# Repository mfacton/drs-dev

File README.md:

# drs-dev
Active Aero Development Board

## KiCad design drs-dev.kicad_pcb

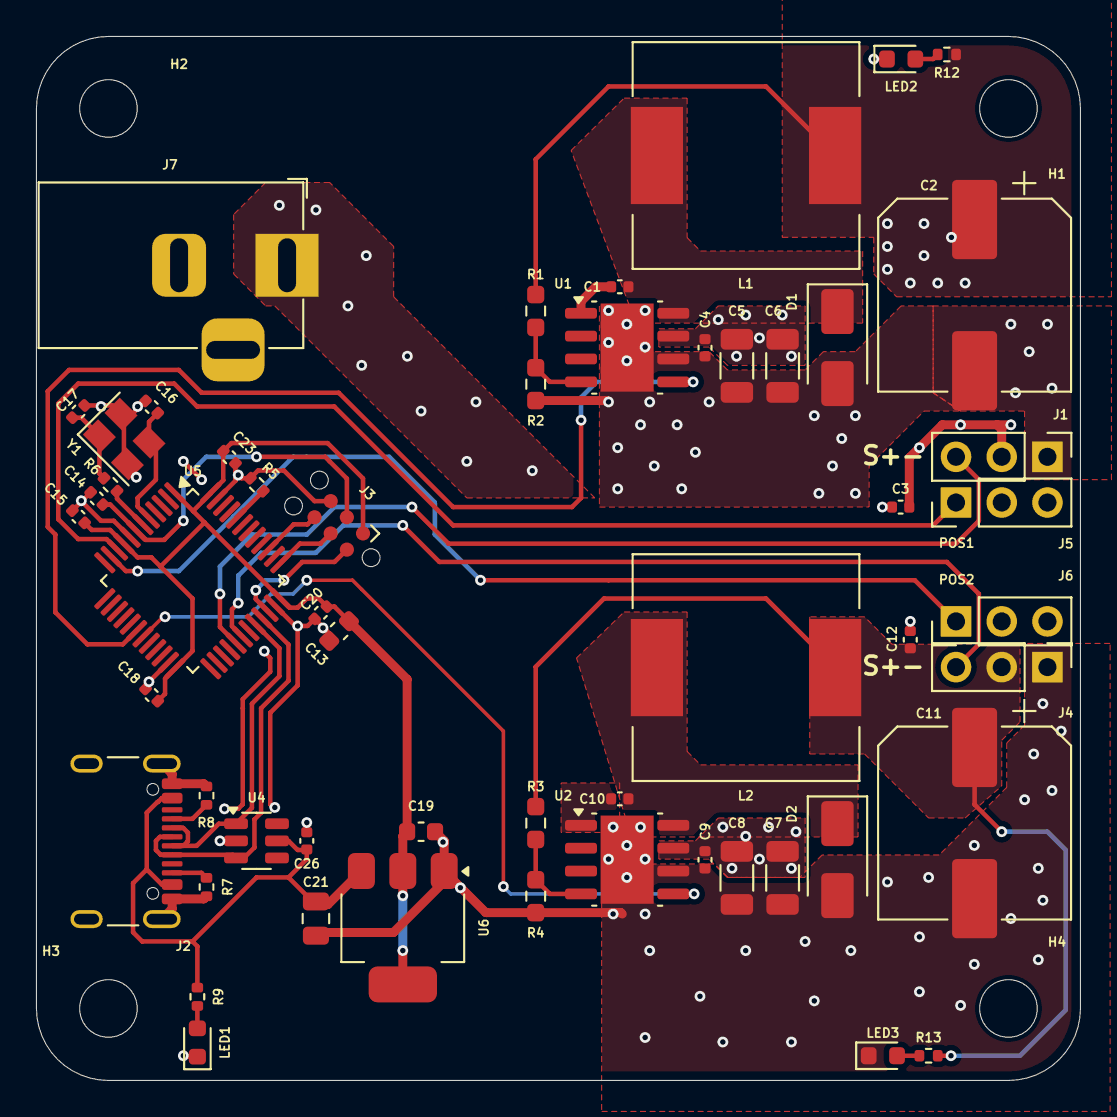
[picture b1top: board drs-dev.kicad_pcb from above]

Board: 2 copper layers, 58.0 x 58.0 mm, 58 parts (0 on the bottom side), 33 nets.

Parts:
C1, C3, C4, C9, C10, C12: 10n; C_0402_1005Metric
C2, C11: 330u; CP_Elec_10x10.5
C5, C6, C7, C8: 10u; C_1206_3216Metric
C13: 10u; C_0603_1608Metric
C14, C15, C18, C20, C23: 100n; C_0402_1005Metric
C16, C17: 10p; C_0402_1005Metric
C19: 22u; C_0603_1608Metric
C21: 22u; C_0805_2012Metric
C26: 1u; C_0402_1005Metric
D1, D2: SS54; D_SMA
H1, H2, H3, H4: MountingHole; MountingHole_3.2mm_M3
J1, J4, J5, J6: Conn_01x03_Pin; PinHeader_1x03_P2.54mm_Vertical
J2: USB_C_Receptacle_USB2.0_16P; USB_C_Receptacle_GCT_USB4105-xx-A_16P_TopMnt_Horizontal
J3: Conn_ARM_SWD_TagConnect_TC2030-NL; Tag-Connect_TC2030-IDC-NL_2x03_P1.27mm_Vertical
J7: Barrel_Jack_Switch; BarrelJack_Horizontal
L1, L2: 15u; L_12x12mm_H4.5mm
LED1: LEDG; LED_0603_1608Metric
LED2, LED3: LEDB; LED_0603_1608Metric
R1, R3: 10k; R_0603_1608Metric_Pad0.98x0.95mm_HandSolder
R2, R4: 3k3; R_0603_1608Metric_Pad0.98x0.95mm_HandSolder
R5: 10k; R_0402_1005Metric
R6: 330; R_0402_1005Metric
R7, R8: 5k1; R_0402_1005Metric
R9, R12, R13: 1k; R_0402_1005Metric
U1, U2: TPS5450DDAR; Texas_R-PDSO-G8_EP2.95x4.9mm_Mask2.4x3.1mm
U4: SRV05-4; SOT-23-6
U5: STM32F103C8Tx; LQFP-48_7x7mm_P0.5mm
U6: AMS1117-3.3; SOT-223-3_TabPin2
Y1: 16MHz; Crystal_SMD_3225-4Pin_3.2x2.5mm

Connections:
+3V3: C13.1, C15.1, C18.1, C19.1, C20.1, C23.1, J3.1 (VCC), U5.1 (VBAT), U5.9 (VDDA), U5.24 (VDD), U5.36 (VDD), U5.48 (VDD), U6.2 (VO)
+12V: C4.1, C5.1, C6.1, C7.1, C8.1, C9.1, J7.1, U1.7 (VIN), U2.7 (VIN)
/BOOT0: R5.1, U5.44 (BOOT0)
/EN1: U1.5 (ENA), U5.18 (PB0)
/EN2: U2.5 (ENA), U5.19 (PB1)
/POS1: J5.1, U5.10 (PA0)
/POS2: J6.1, U5.11 (PA1)
/PWM1: J1.3, U5.29 (PA8)
/PWM2: J4.3, U5.30 (PA9)
/PWR1: C2.1, C3.1, J1.2, L1.2, R1.1, R12.1
/PWR2: C11.1, C12.1, J4.2, L2.2, R3.1, R13.1
/RST: C14.1, J3.3 (~RESET), U5.7 (NRST)
/Regulator1/BOOT: C1.2, U1.1 (BOOT)
/Regulator1/LED: LED2.2 (A), R12.2
/Regulator1/PH: C1.1, D1.1 (K), L1.1, U1.8 (PH)
/Regulator1/VSNS: R1.2, R2.1, U1.4 (VSNS)
/Regulator2/BOOT: C10.2, U2.1 (BOOT)
/Regulator2/LED: LED3.2 (A), R13.2
/Regulator2/PH: C10.1, D2.1 (K), L2.1, U2.8 (PH)
/Regulator2/VSNS: R3.2, R4.1, U2.4 (VSNS)
/SWCLK: J3.4 (SWCLK), U5.37 (PA14)
/SWDIO: J3.2 (SWDIO), U5.34 (PA13)
/SWO: J3.6 (SWO), U5.39 (PB3)
/USB_D+: J2.A6 (D+), J2.B6 (D+), U4.3 (IO2), U5.33 (PA12)
/USB_D-: J2.A7 (D-), J2.B7 (D-), U4.1 (IO1), U5.32 (PA11)
/VBLED: LED1.2 (A), R9.2
/XTALI: C16.2, U5.5 (PD0), Y1.3
/XTALO: R6.2, U5.6 (PD1)
/XTALR: C17.2, R6.1, Y1.1
GND: C2.2, C3.2, C4.2, C5.2, C6.2, C7.2, C8.2, C9.2, C11.2, C12.2, C13.2, C14.2, C15.2, C16.1, C17.1, C18.2, C19.2, C20.2, C21.2, C23.2, C26.2, D1.2 (A), D2.2 (A), J1.1, J2.A1 (GND), J2.A12 (GND), J2.B1 (GND), J2.B12 (GND), J2.S1 (SHIELD), J3.5 (GND), J4.1, J7.2, LED1.1 (K), LED2.1 (K), LED3.1 (K), R2.2, R4.2, R5.2, R7.2, R8.2, U1.6 (GND), U1.9 (PAD), U2.6 (GND), U2.9 (PAD), U4.2 (VN), U5.8 (VSSA), U5.23 (VSS), U5.35 (VSS), U5.47 (VSS), U6.1 (GND), Y1.2, Y1.4
unnamed: J2.A5 (CC1), R8.1
unnamed: J2.B5 (CC2), R7.1
VBUS: C21.1, C26.1, J2.A4 (VBUS), J2.A9 (VBUS), J2.B4 (VBUS), J2.B9 (VBUS), R9.1, U4.5 (VP), U6.3 (VI)

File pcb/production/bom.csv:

Designator,Footprint,Quantity,Value,LCSC Part #
"C1, C10, C12, C3, C4, C9",0402,6,10n,
"C11, C2",CP_Elec_10x10.5,2,330u,C280411
C13,0603,1,10u,
"C14, C15, C18, C20, C23",0402,5,100n,
"C16, C17",0402,2,10p,
C19,0603,1,22u,
C21,0805,1,22u,
C26,0402,1,1u,
"C5, C6, C7, C8",1206,4,10u,C13585
"D1, D2",D_SMA,2,SS54,
J2,USB_C_Receptacle_GCT_USB4105-xx-A_16P_TopMnt_Horizontal,1,USB_C_Receptacle_USB2.0_16P,C165948
J7,BarrelJack_Horizontal,1,Barrel_Jack_Switch,C319099
"L1, L2",L_12x12mm_H4.5mm,2,15u,C149596
LED1,0603,1,LEDG,C2986059
"LED2, LED3",0603,2,LEDB,C2986058
"R1, R3",0603,2,10k,
R10,0402,1,1k5,C25867
"R12, R13, R9",0402,3,1k,
"R2, R4",0603,2,3k3,
R5,0402,1,10k,
R6,0402,1,330,
"R7, R8",0402,2,5k1,
"U1, U2",Texas_R-PDSO-G8_EP2.95x4.9mm_Mask2.4x3.1mm,2,TPS5450DDAR,C114425
U4,SOT-23-6,1,SRV05-4,C7420376
U5,LQFP-48_7x7mm_P0.5mm,1,STM32F103C8Tx,
U6,SOT-223-3_TabPin2,1,AMS1117-3.3,
Y1,Crystal_SMD_3225-4Pin_3.2x2.5mm,1,16MHz,

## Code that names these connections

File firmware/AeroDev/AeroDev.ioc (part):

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Mcu.Name=STM32F103C(8-B)Tx
Mcu.Package=LQFP48
Mcu.UserName=STM32F103C8Tx
PA0-WKUP.Signal=ADCx_IN0
PA1.Signal=ADCx_IN1
PA11.Mode=Device
PA11.Signal=USB_DM
PA12.Mode=Device
PA12.Signal=USB_DP
PA13.Mode=Trace_Asynchronous_SW
PA13.Signal=SYS_JTMS-SWDIO
PA14.Mode=Trace_Asynchronous_SW
PA14.Signal=SYS_JTCK-SWCLK
PA8.Signal=S_TIM1_CH1
PA9.Signal=S_TIM1_CH2
PB3.Mode=Trace_Asynchronous_SW
PB3.Signal=SYS_JTDO-TRACESWO
PD0-OSC_IN.Mode=HSE-External-Oscillator
PD0-OSC_IN.Signal=RCC_OSC_IN
PD1-OSC_OUT.Mode=HSE-External-Oscillator
PD1-OSC_OUT.Signal=RCC_OSC_OUT
RCC.HSEDivPLL=RCC_HSE_PREDIV_DIV2
RCC.HSE_VALUE=16000000
RCC.SYSCLKFreq_VALUE=72000000
RCC.SYSCLKSource=RCC_SYSCLKSOURCE_PLLCLK
board=custom

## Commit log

2024-06-14 Add gitignore
2024-06-14 Transfer Project
2024-06-19 Add labels and fix pinout
2024-06-19 Generate fab files
2024-06-23 Fix usb pullup and generate new fab files
2024-09-13 Move pcb to pcb folder
2024-09-13 Add firmware
